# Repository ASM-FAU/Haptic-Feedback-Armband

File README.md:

# Haptic Feedback Armband

The haptic feedback armband was mainly designed for prosthesis appliacations. It contains 5 vibration motors, of which each can correspond to one finger. The device is completely wireless and contains a custom designed PCB, 1800 mAh lithium polymer battery, 5 vibration motors, an IMU to gather motion data and an FSR to measure armband tightness. All code and hardware models are provided in this repository to replicate the device.

## Software
The software is split into two parts for the client device (the haptic feedback armband) and a master PC that it communicates with. The architecture is shown in the follong Figure.

## Hardware
The armband consists of 5 modules in total. A main module, containing the PCB, battery and senors as well as a vibration motor and smaller modules containing a vibration motor only. The casing was 3D printed using FDM and PLA filament. The flexible links were printed with TPU filament. This is how the armband looks like:

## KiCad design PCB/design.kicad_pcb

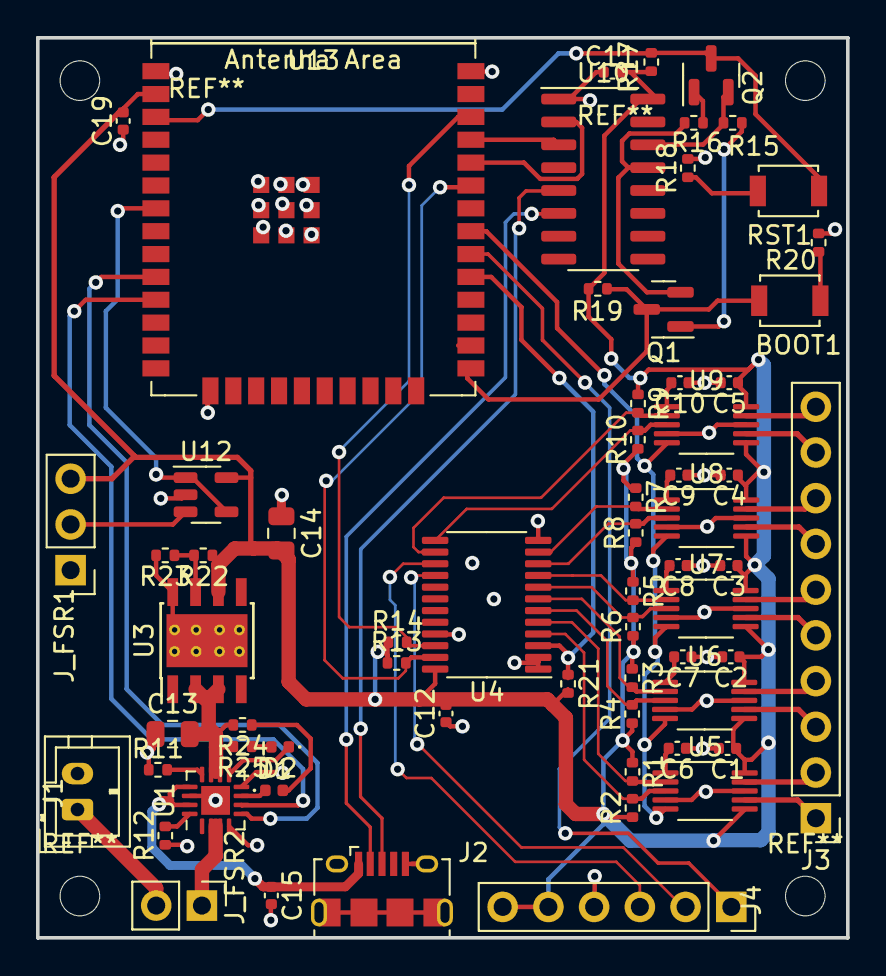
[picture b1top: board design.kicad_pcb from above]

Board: 2 copper layers, 45.0 x 50.0 mm, 64 parts (0 on the bottom side), 61 nets.

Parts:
BOOT1: SW_DPST_x2; SW_SPST_B3U-1000P
C1, C2, C3, C4, C5, C6, C7, C8, C9, C10: 1uF; C_0402_1005Metric
C11, C12, C15, C19: 10uF; C_0402_1005Metric
C13, C14: 47uF; C_0805_2012Metric
D1, D2: LED; LED_0402_1005Metric
J1: Conn_01x02_Female; JST_PH_B2B-PH-K_1x02_P2.00mm_Vertical
J2: USB_B_Micro; USB_Micro-B_Amphenol_10118194_Horizontal
J3: Conn_01x10_Male; PinHeader_1x10_P2.54mm_Vertical
J4: Conn_01x06_Male; PinSocket_1x06_P2.54mm_Vertical
J_FSR1: Conn_01x03_Female; PinHeader_1x03_P2.54mm_Vertical
J_FSR2: Conn_01x02_Female; PinHeader_1x02_P2.54mm_Vertical
Q1, Q2: BC848; SOT-23
R1, R2, R3, R4, R5, R6, R7, R8, R9, R10: 2.2kOhm; R_0402_1005Metric
R11: 1.1kOhm; R_0402_1005Metric
R12: 604Ohm; R_0402_1005Metric
R13, R14, R21: 4.7kOhm; R_0402_1005Metric
R15, R16, R17, R19: 10kOhm; R_0402_1005Metric
R18, R20: 470 Ohm; R_0402_1005Metric
R22: 169kOhm; R_0402_1005Metric
R23: 30.1kOhm; R_0402_1005Metric
R24, R25: 1.5kOhm; R_0402_1005Metric
RST1: SW_DPST_x2; SW_SPST_B3U-1000P
U1: BQ24072RGT; VQFN-16-1EP_3x3mm_P0.5mm_EP1.6x1.6mm
U3: TPS7A7001DDA; TI_SO-PowerPAD-8_ThermalVias
U4: TCA9548APWR; TSSOP-24_4.4x7.8mm_P0.65mm
U5, U6, U7, U8, U9: DRV2605LDGS; VSSOP-10_3x3mm_P0.5mm
U10: CH340G; SOIC-16_3.9x9.9mm_P1.27mm
U12: MCP601-xOT; SOT-23-5
U13: ESP32-WROOM-E; ESP32-WROOM-32E

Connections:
+5V: C15.1, J2.1 (VBUS), U1.13 (IN), U1.15 (TD)
BAT_EN1: U1.6 (EN1), U13.11 (DAC_2/ADC2_CH9/GPIO26)
BAT_EN2: U1.5 (EN2), U13.10 (DAC_1/ADC2_CH8/GPIO25)
BAT_OUT: C13.2, R24.2, R25.2, U1.10 (OUT), U1.11 (OUT), U3.2 (EN), U3.3 (IN)
BNO_SCL: J4.2, U4.16 (SC5)
BNO_SDA: J4.3, U4.15 (SD5)
DRV_EN: U5.5 (EN), U6.5 (EN), U7.5 (EN), U8.5 (EN), U9.5 (EN), U13.31 (GPIO19)
EN: Q2.3 (C), R17.2, RST1.1 (A), U13.3 (EN/CHIP_PU)
FSR_AI: U12.1, U12.4 (-), U13.7 (GPIO35/ADC1_CH7)
GND: C1.2, C2.2, C3.2, C4.2, C5.2, C6.1, C7.1, C8.1, C9.1, C10.1, C11.1, C12.1, C13.1, C14.1, C15.2, C19.1, J1.2, J2.5 (GND), J2.6 (Shield), J4.4, J_FSR1.1, R11.1, R12.1, R18.2, R20.2, R23.2, U1.4 (~CE), U1.8 (VSS), U1.14 (TMR), U1.17 (VSS), U3.8 (GND), U3.9 (EP), U4.1 (A0), U4.2 (A1), U4.12 (GND), U4.21 (A2), U5.4 (IN/TRIG), U5.8 (GND), U6.4 (IN/TRIG), U6.8 (GND), U7.4 (IN/TRIG), U7.8 (GND), U8.4 (IN/TRIG), U8.8 (GND), U9.4 (IN/TRIG), U9.8 (GND), U10.1 (GND), U12.2 (V-), U13.1 (GND), U13.15 (GND), U13.38 (GND), U13.39 (GND_THERMAL)
IMU_RST: J4.1, U13.30 (GPIO18)
IO0: BOOT1.1 (A), Q1.3 (C), R19.2, U13.25 (GPIO0/BOOT/ADC2_CH1)
unnamed: BOOT1.2 (B), R20.1
unnamed: D1.2 (A), R24.1
unnamed: D1.1 (K), U1.7 (~PGOOD)
unnamed: D2.2 (A), R25.1
unnamed: D2.1 (K), U1.9 (~CHG)
unnamed: J1.1, J_FSR2.2
unnamed: J_FSR1.2, U12.3 (+)
unnamed: J_FSR2.1, U1.2 (BAT), U1.3 (BAT)
unnamed: Q1.1 (B), R15.1
unnamed: Q1.2 (E), R16.1, U10.13 (~DTR)
unnamed: Q2.1 (B), R16.2
unnamed: Q2.2 (E), R15.2, U10.14 (~RTS)
unnamed: R18.1, RST1.2 (B)
unnamed: R11.2, U1.12 (ILIM)
unnamed: R12.2, U1.16 (ISET)
unnamed: R22.2, R23.1, U3.7 (FB)
unnamed: C6.2, U5.1 (REG)
unnamed: C7.2, U6.1 (REG)
unnamed: C8.2, U7.1 (REG)
unnamed: C9.2, U8.1 (REG)
unnamed: C10.2, U9.1 (REG)
RXD: U10.2 (TXD), U13.34 (U0RXD/GPIO3)
SC0: R1.2, U4.5 (SC0), U5.2 (SCL)
SC1: R3.2, U4.7 (SC1), U6.2 (SCL)
SC2: R5.2, U4.9 (SC2), U7.2 (SCL)
SC3: R7.2, U4.11 (SC3), U8.2 (SCL)
SC4: R9.2, U4.14 (SC4), U9.2 (SCL)
SCL_multiplexer: R14.2, U4.22 (SCL), U13.36 (GPIO22)
SD0: R2.2, U4.4 (SD0), U5.3 (SDA)
SD1: R4.2, U4.6 (SD1), U6.3 (SDA)
SD2: R6.2, U4.8 (SD2), U7.3 (SDA)
SD3: R8.2, U4.10 (SD3), U8.3 (SDA)
SD4: R10.2, U4.13 (SD4), U9.3 (SDA)
SDA_multiplexer: R13.2, U4.23 (SDA), U13.33 (GPIO21)
TXD: U10.3 (RXD), U13.35 (U0TXD/GPIO1)
UD+: J2.3 (D+), U10.5 (UD+)
UD-: J2.2 (D-), U10.6 (UD-)
VDD: C1.1, C2.1, C3.1, C4.1, C5.1, C11.2, C12.2, C14.2, C19.2, J4.5, J4.6, J_FSR1.3, R1.1, R2.1, R3.1, R4.1, R5.1, R6.1, R7.1, R8.1, R9.1, R10.1, R13.1, R14.1, R17.1, R19.1, R21.2, R22.1, U3.6 (OUT), U4.24 (VCC), U5.6 (VDD/NC), U5.10 (VDD), U6.6 (VDD/NC), U6.10 (VDD), U7.6 (VDD/NC), U7.10 (VDD), U8.6 (VDD/NC), U8.10 (VDD), U9.6 (VDD/NC), U9.10 (VDD), U10.16 (VCC), U12.5 (V+), U13.2 (3V3)
drv_out_0+: J3.1, U5.7 (OUT+)
drv_out_0-: J3.2, U5.9 (OUT-)
drv_out_1+: J3.3, U6.7 (OUT+)
drv_out_1-: J3.4, U6.9 (OUT-)
drv_out_2+: J3.5, U7.7 (OUT+)
drv_out_2-: J3.6, U7.9 (OUT-)
drv_out_3+: J3.7, U8.7 (OUT+)
drv_out_3-: J3.8, U8.9 (OUT-)
drv_out_4+: J3.9, U9.7 (OUT+)
drv_out_4-: J3.10, U9.9 (OUT-)
i2C_Multi_reset: R21.1, U4.3 (~RESET), U13.29 (GPIO5)

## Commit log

2024-02-14 Add files via upload
    initial upload
